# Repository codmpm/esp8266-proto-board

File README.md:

# ESP8266 minimal proto board / breadboard adaptor

This is a simple yet useful breadboard adaptor for the all famous ESP8266.

I've built this as the cheap chinese ones (white boards) are to wide to fit on a regular breadboard. To develop an own design you often don't need a full grown [Adafruit Huzzah](https://www.adafruit.com/product/2471), [Olimex MOD-WIFI-ESP8266-DEV](https://www.olimex.com/Products/IoT/MOD-WIFI-ESP8266-DEV/open-source-hardware) or similar ESP8266 devboard. Also the cheap chinese ones don't have a reset and/or flash button. I don't want to wire the needed resistors and a flash/reset button every time I'm putting an ESP on a breadboard.

Inside the folders you'll find the Eagle schematics and board files.

## Schematics

## Get it working...
You can simply solder some male headers and an ESP-12(E/F/Q), ESP-07 or ESP-14 on top of the board and are ready to go. 

The better way will be to at least solder some `10kΩ` resistors (`R1-R5`) to have the needed pull-ups/pull-downs to get the ESP working. Obviously it is also a good idea to solder the two push buttons so you have the reset and flash functionality. Then power it up with 3.3 Volts and you are good to go.

The buttons are the very common 6x6mm variant which goes by `switch-omron`. In Germany you can source the from [Reichelt](https://www.reichelt.de/Kurzhubtaster/TASTER-9302/3/index.html?ACTION=3&LA=2&ARTICLE=44579&GROUPID=7587&artnr=TASTER+9302&SEARCH=%252A) for example. But every electronics shop should have them in stock.

Optionally you can solder an [LDO](https://en.wikipedia.org/wiki/Low-dropout_regulator) to power the ESP with more than 3.3 Volts, as shown on the left side:

## 0805 Version

You'll need 5 x SMD 0805 `10kΩ` resistors (`R1-R5`) and the two push-buttons. The 0805 resistors should be available from your prefered electronic store.

If you want to use the LDO you need the [AP2210K](https://www.diodes.com/assets/Datasheets/AP2210.pdf), a `SOT-23-5` LDO which can be powered with up to 13.2 Volts and only needs two capacitors (`C1/C2`) to run smooth. `C1` is `1µF`, `C2` is `2.2µF` in a 0805 package. It delivers up to 300mA which is fairly enough to power the ESP8266 - you have some room for periphals ;-)

You can use any other `SOT-32-5` LDO which supplies 3.3 Volts with at least 120-150mA, is satisfied with two capacitors and has the same pinout.

The boards can be ordered from [OSH Park](https://oshpark.com/shared_projects/u6mogmdg)

## 1206 Version
This is not finished yet and the repo only holds the work-in-progress version...

## Credits
Patrik Mayer, cod.m GmbH, 2017

Inspired by [tiny ESP8266 breakout](https://github.com/skorokithakis/tiny-ESP8266-breakout) from Stavros Korokithakis

## License
[CC-BY-SA](https://creativecommons.org/licenses/by-sa/3.0/)

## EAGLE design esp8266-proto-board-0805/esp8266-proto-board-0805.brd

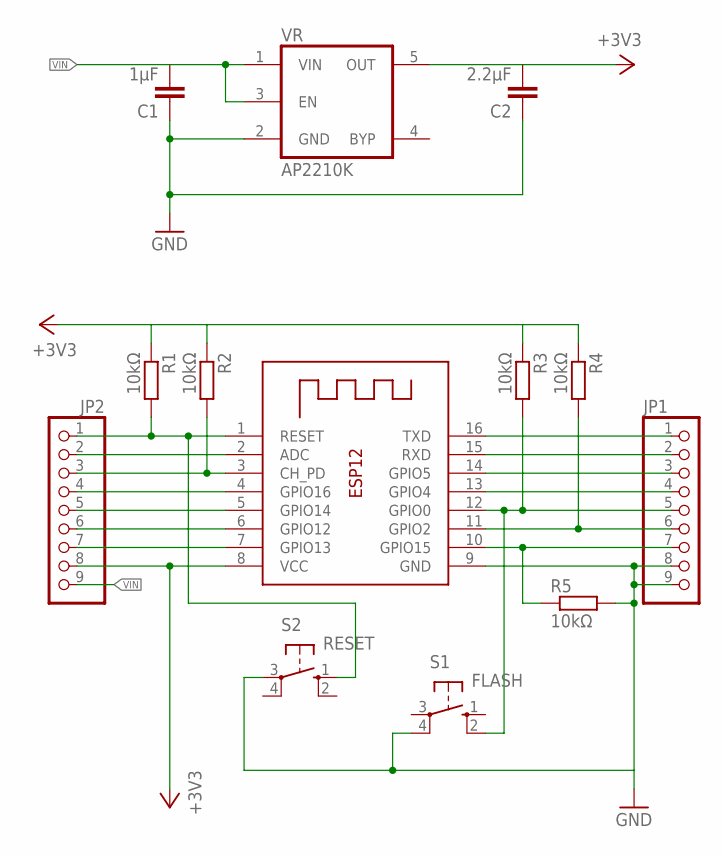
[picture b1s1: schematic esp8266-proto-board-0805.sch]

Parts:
C1: 1µF; C0805K
C2: 2.2µF; C0805K
JP1, JP2: PINHD-1X9; 1X09-BIG
R1, R2, R3, R4, R5: 10kΩ; R0805W
S1: FLASH; B3F-10XX
S2: RESET; B3F-10XX
U1: ESP-12
VR: AP2210K; SOT23-5

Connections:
+3V3: C2.2, JP2.8, R1.1, R2.1, R3.1, R4.1, U1.8 (VCC), VR.5 (OUT)
ADC: JP2.2, U1.2 (ADC)
CH_PD: JP2.3, R2.2, U1.3 (CH_PD)
GND: C1.1, C2.1, JP1.8, JP1.9, R5.2, S1.4 (P1), S2.3, U1.9 (GND), VR.2 (GND)
GPIO0: JP1.5, R3.2, S1.2 (S1), U1.12 (GPIO0)
GPIO2: JP1.6, R4.2, U1.11 (GPIO2)
GPIO4: JP1.4, U1.13 (GPIO4)
GPIO5: JP1.3, U1.14 (GPIO5)
GPIO12: JP2.6, U1.6 (GPIO12)
GPIO13: JP2.7, U1.7 (GPIO13)
GPIO14: JP2.5, U1.5 (GPIO14)
GPIO15: JP1.7, R5.1, U1.10 (GPIO15)
GPIO16: JP2.4, U1.4 (GPIO16)
RST: JP2.1, R1.2, S2.1 (S), U1.1 (RESET)
RX: JP1.2, U1.15 (RXD)
TX: JP1.1, U1.16 (TXD)
VIN: C1.2, JP2.9, VR.1 (VIN), VR.3 (EN)

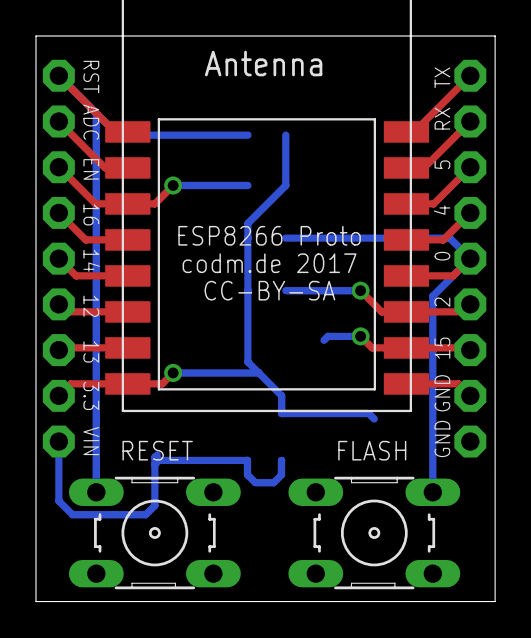
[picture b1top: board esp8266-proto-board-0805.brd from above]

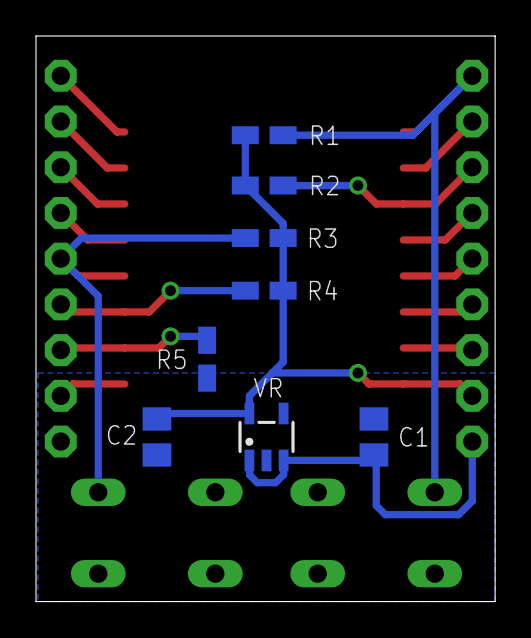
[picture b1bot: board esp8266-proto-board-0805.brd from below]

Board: 2 copper layers, 25.5 x 31.4 mm, 13 parts (8 on the bottom side), 17 nets.

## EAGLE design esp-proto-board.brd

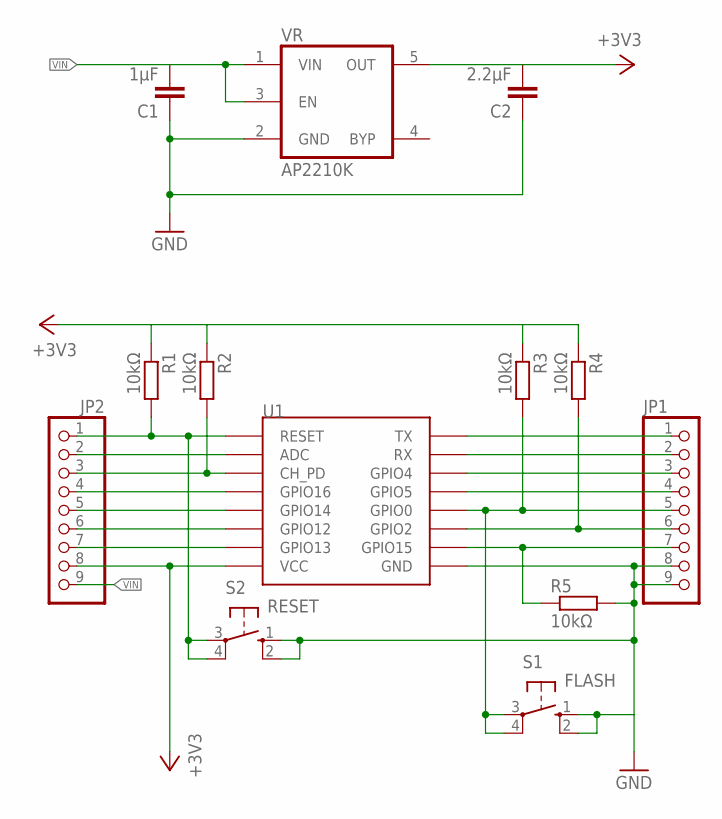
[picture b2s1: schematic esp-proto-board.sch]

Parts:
C1: 1µF; C0805K
C2: 2.2µF; C0805K
JP1, JP2: PINHD-1X9; 1X09
R1, R2, R3, R4, R5: 10kΩ; R0805W
S1: FLASH; B3F-10XX
S2: RESET; B3F-10XX
U1: ESP12SMD; ESP12-SMD
VR: AP2210K; SOT23-5

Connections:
+3V3: C2.2, JP2.8, R1.1, R2.1, R3.1, R4.1, U1.VCC, VR.5 (OUT)
ADC: JP2.2, U1.ADC
CH_PD: JP2.3, R2.2, U1.CH_PD
GND: C1.1, C2.1, JP1.8, JP1.9, R5.2, S1.1 (S), S1.2 (S1), S2.1 (S), S2.2 (S1), U1.GND, VR.2 (GND)
GPIO0: JP1.5, R3.2, S1.3, S1.4 (P1), U1.GPIO0
GPIO2: JP1.6, R4.2, U1.GPIO2
GPIO4: JP1.3, U1.GPIO4
GPIO5: JP1.4, U1.GPIO5
GPIO12: JP2.6, U1.GPIO12
GPIO13: JP2.7, U1.GPIO13
GPIO14: JP2.5, U1.GPIO14
GPIO15: JP1.7, R5.1, U1.GPIO15
GPIO16: JP2.4, U1.GPIO16
RST: JP2.1, R1.2, S2.3, S2.4 (P1), U1.RESET
RX: JP1.2, U1.RXD0 (RX)
TX: JP1.1, U1.TXD0 (TX)
VIN: C1.2, JP2.9, VR.1 (VIN), VR.3 (EN)

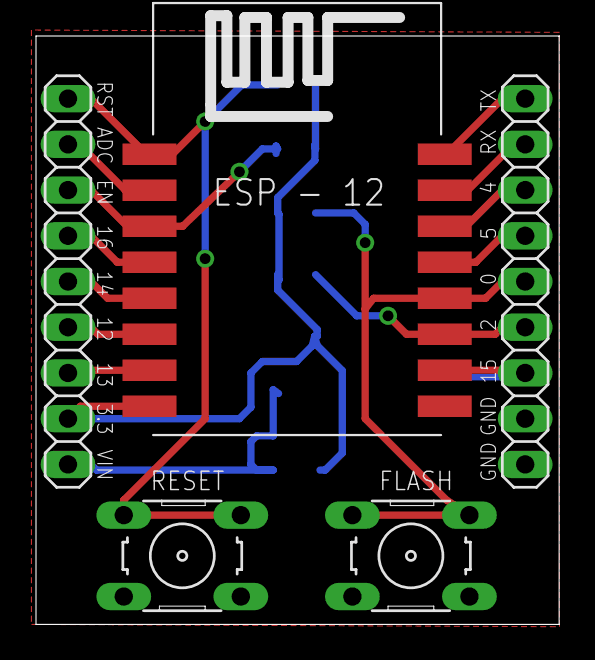
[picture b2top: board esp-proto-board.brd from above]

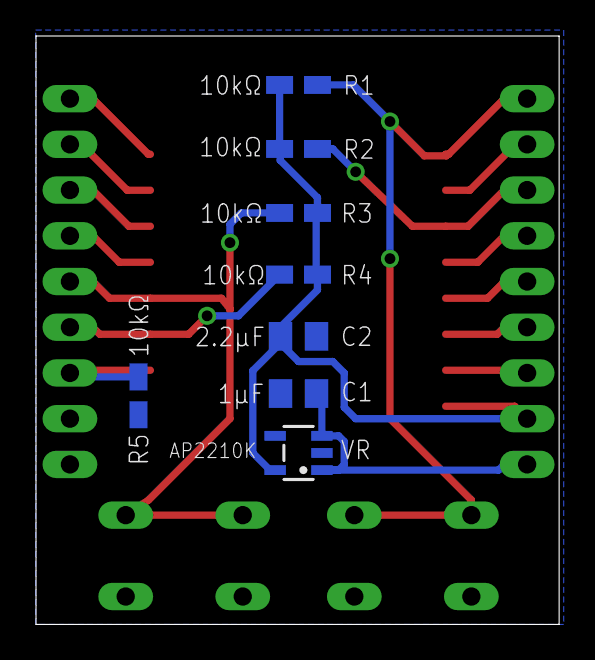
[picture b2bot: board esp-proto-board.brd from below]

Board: 2 copper layers, 29.1 x 32.7 mm, 13 parts (8 on the bottom side), 17 nets.

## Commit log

2017-04-08 moved bValues to bNames
2017-04-08 added board images
2017-04-19 reworked 0805 version with better footprint
2017-04-19 moved capacitors
2017-05-03 tested ordered 0805 version, first public release
2017-05-03 refined readme
2017-05-11 fixed mixed up gpio5/gpio4 in esp-lib part
2017-05-13 new oshpark link
